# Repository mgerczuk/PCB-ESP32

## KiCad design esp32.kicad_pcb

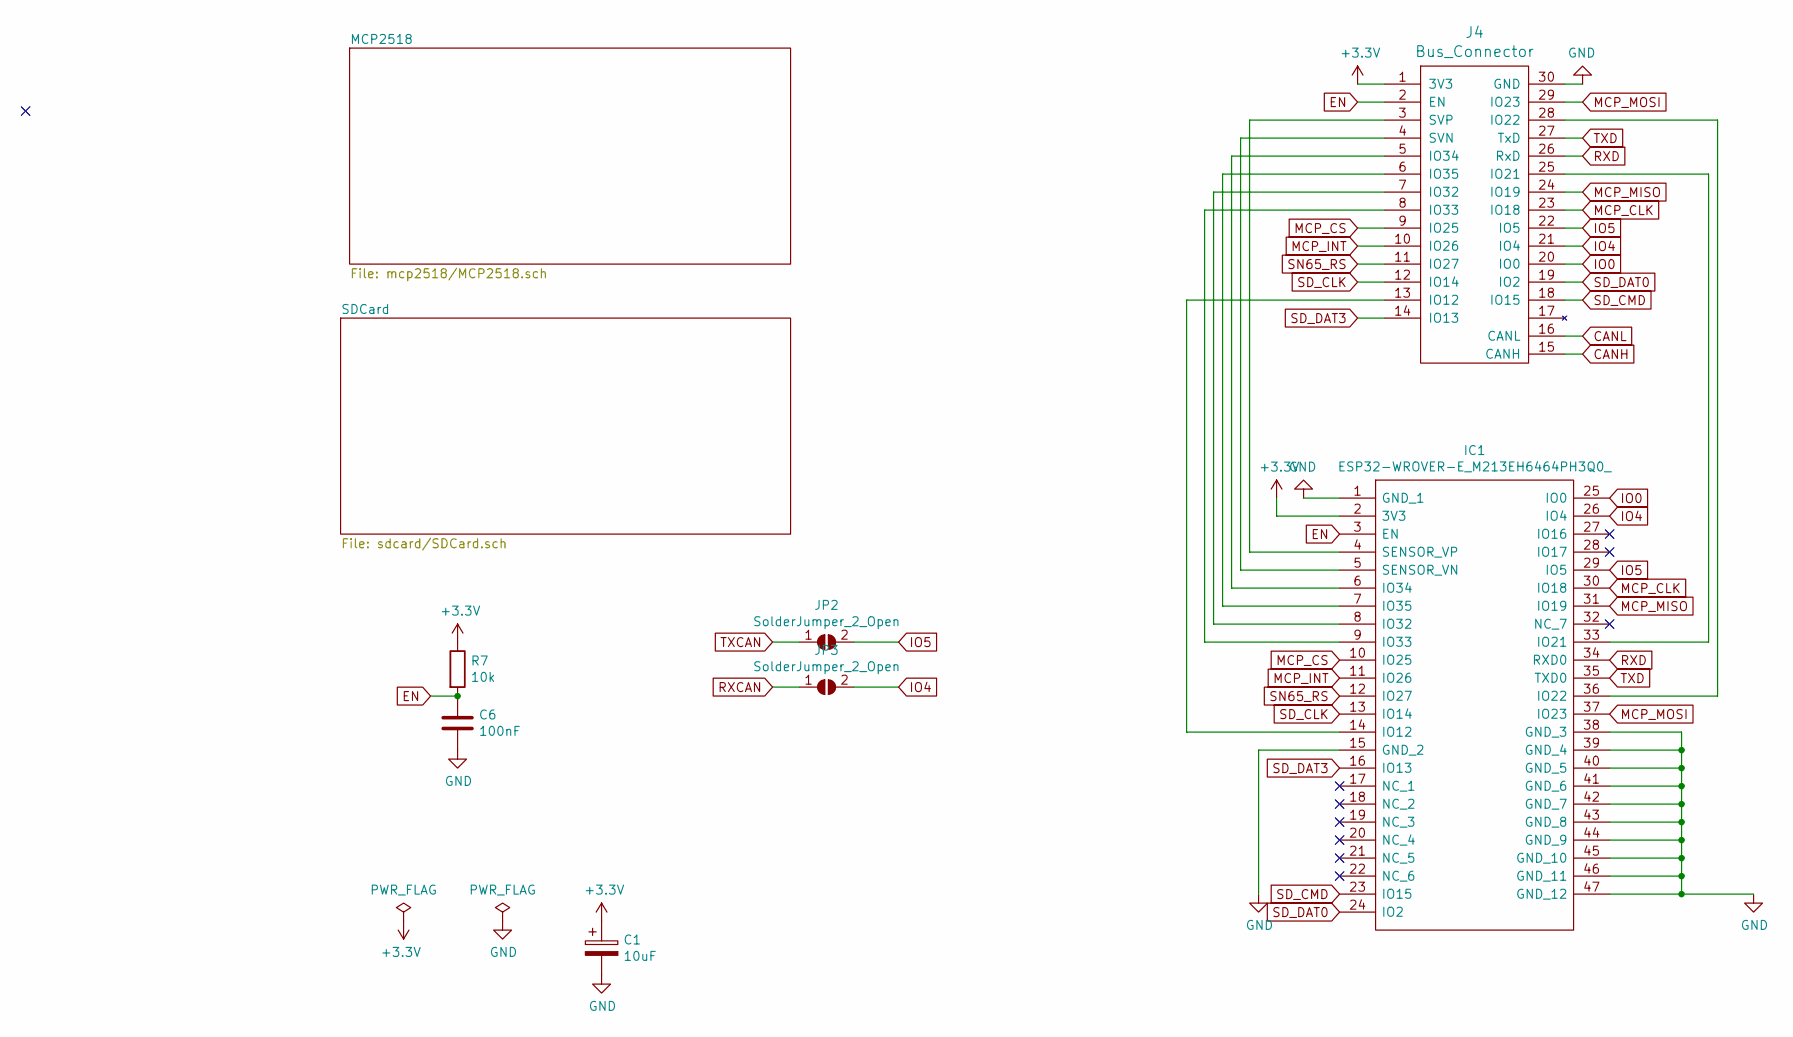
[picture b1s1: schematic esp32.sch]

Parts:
C1: 10uF; CP_EIA-3528-21_Kemet-B_Pad1.50x2.35mm_HandSolder
C6: 100nF; C_0603_1608Metric_Pad1.08x0.95mm_HandSolder
IC1: ESP32-WROVER-E_M213EH6464PH3Q0_; ESP32WROVER; Mouser Part Number 356-ESP32WRVE26464PC
J4: Bus_Connector; PinHeader
JP2, JP3: SolderJumper_2_Open; SolderJumper-2_P1.3mm_Open_RoundedPad1.0x1.5mm
R7: 10k; R_0603_1608Metric_Pad0.98x0.95mm_HandSolder

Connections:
+3V3: C1.1, IC1.2 (3V3), J4.1 (3V3), R7.1; also elsewhere on the board
CANH: J4.15 (CANH); also elsewhere on the board
CANL: J4.16 (CANL); also elsewhere on the board
EN: C6.1, IC1.3 (EN), J4.2 (EN), R7.2
GND: C1.2, C6.2, IC1.1 (GND_1), IC1.15 (GND_2), IC1.38 (GND_3), IC1.39 (GND_4), IC1.40 (GND_5), IC1.41 (GND_6), IC1.42 (GND_7), IC1.43 (GND_8), IC1.44 (GND_9), IC1.45 (GND_10), IC1.46 (GND_11), IC1.47 (GND_12), J4.30 (GND); also elsewhere on the board
IO0: IC1.25 (IO0), J4.20 (IO0)
IO4: IC1.26 (IO4), J4.21 (IO4), JP3.2 (B)
IO5: IC1.29 (IO5), J4.22 (IO5), JP2.2 (B)
MCP_CLK: IC1.30 (IO18), J4.23 (IO18); also elsewhere on the board
MCP_CS: IC1.10 (IO25), J4.9 (IO25); also elsewhere on the board
MCP_INT: IC1.11 (IO26), J4.10 (IO26); also elsewhere on the board
MCP_MISO: IC1.31 (IO19), J4.24 (IO19); also elsewhere on the board
MCP_MOSI: IC1.37 (IO23), J4.29 (IO23); also elsewhere on the board
unnamed: IC1.4 (SENSOR_VP), J4.3 (SVP)
unnamed: IC1.5 (SENSOR_VN), J4.4 (SVN)
unnamed: IC1.6 (IO34), J4.5 (IO34)
unnamed: IC1.7 (IO35), J4.6 (IO35)
unnamed: IC1.8 (IO32), J4.7 (IO32)
unnamed: IC1.9 (IO33), J4.8 (IO33)
unnamed: IC1.14 (IO12), J4.13 (IO12)
unnamed: IC1.33 (IO21), J4.25 (IO21)
unnamed: IC1.36 (IO22), J4.28 (IO22)
RXCAN: JP3.1 (A); also elsewhere on the board
RXD: IC1.34 (RXD0), J4.26 (RxD)
SD_CLK: IC1.13 (IO14), J4.12 (IO14); also elsewhere on the board
SD_CMD: IC1.23 (IO15), J4.18 (IO15); also elsewhere on the board
SD_DAT0: IC1.24 (IO2), J4.19 (IO2); also elsewhere on the board
SD_DAT3: IC1.16 (IO13), J4.14 (IO13); also elsewhere on the board
SN65_RS: IC1.12 (IO27), J4.11 (IO27); also elsewhere on the board
TXCAN: JP2.1 (A); also elsewhere on the board
TXD: IC1.35 (TXD0), J4.27 (TxD)

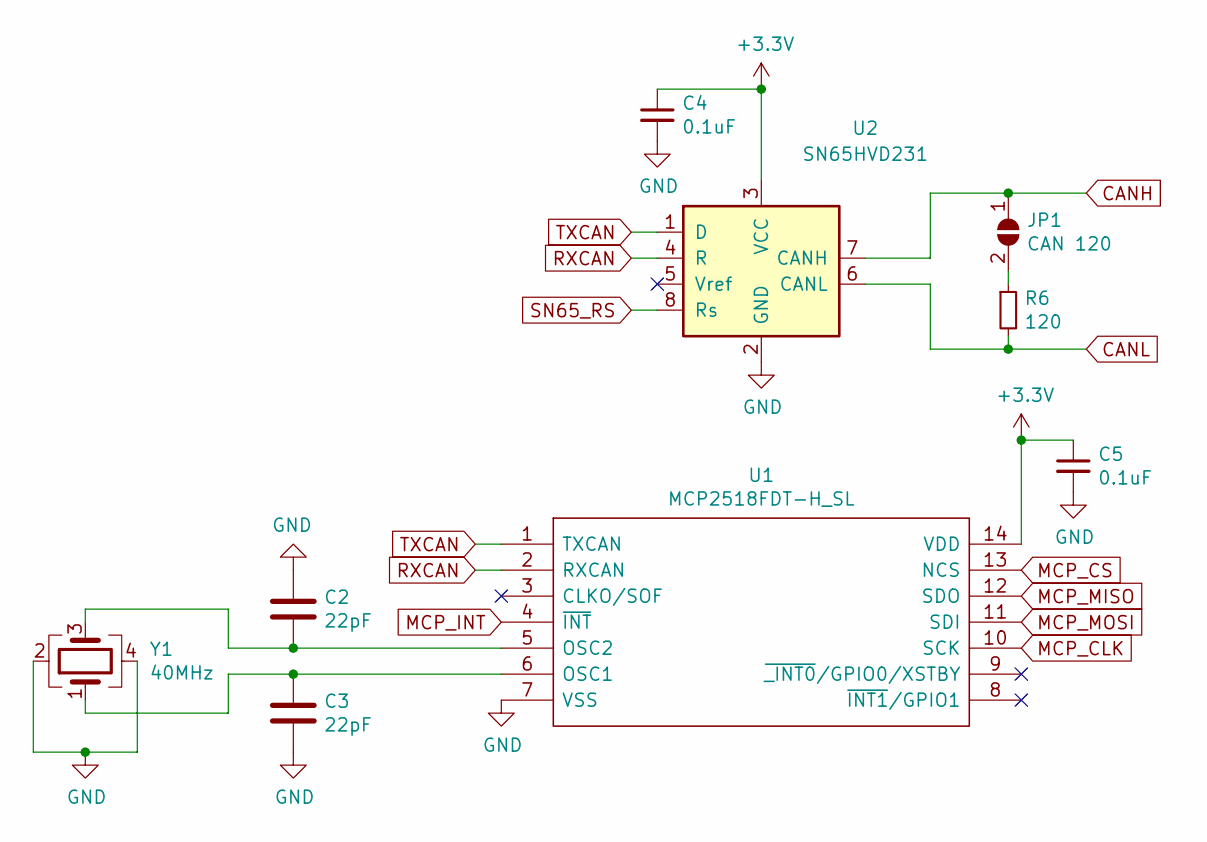
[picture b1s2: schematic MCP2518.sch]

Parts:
C2, C3: 22pF; C_0603_1608Metric_Pad1.08x0.95mm_HandSolder
C4, C5: 0.1uF; C_0603_1608Metric_Pad1.08x0.95mm_HandSolder
JP1: CAN 120; SolderJumper-2_P1.3mm_Open_RoundedPad1.0x1.5mm
R6: 120; R_0603_1608Metric_Pad0.98x0.95mm_HandSolder
U1: MCP2518FDT-H_SL; SOIC127P600X175-14N; Mouser Part Number 579-MCP2518FDT-H/SL
U2: SN65HVD231; SOIC-8_3.9x4.9mm_P1.27mm
Y1: 40MHz; Crystal_SMD_3225-4Pin_3.2x2.5mm

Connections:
+3V3: C4.1, C5.1, U1.14 (VDD), U2.3 (VCC); also elsewhere on the board
CANH: JP1.1 (A), U2.7 (CANH); also elsewhere on the board
CANL: R6.2, U2.6 (CANL); also elsewhere on the board
GND: C2.1, C3.2, C4.2, C5.2, U1.7 (VSS), U2.2 (GND), Y1.2, Y1.4; also elsewhere on the board
MCP_CLK: U1.10 (SCK); also elsewhere on the board
MCP_CS: U1.13 (NCS); also elsewhere on the board
MCP_INT: U1.4 (~INT); also elsewhere on the board
MCP_MISO: U1.12 (SDO); also elsewhere on the board
MCP_MOSI: U1.11 (SDI); also elsewhere on the board
unnamed: C2.2, U1.5 (OSC2), Y1.3
unnamed: C3.1, U1.6 (OSC1), Y1.1
unnamed: JP1.2 (B), R6.1
RXCAN: U1.2 (RXCAN), U2.4 (R); also elsewhere on the board
SN65_RS: U2.8 (Rs); also elsewhere on the board
TXCAN: U1.1 (TXCAN), U2.1 (D); also elsewhere on the board

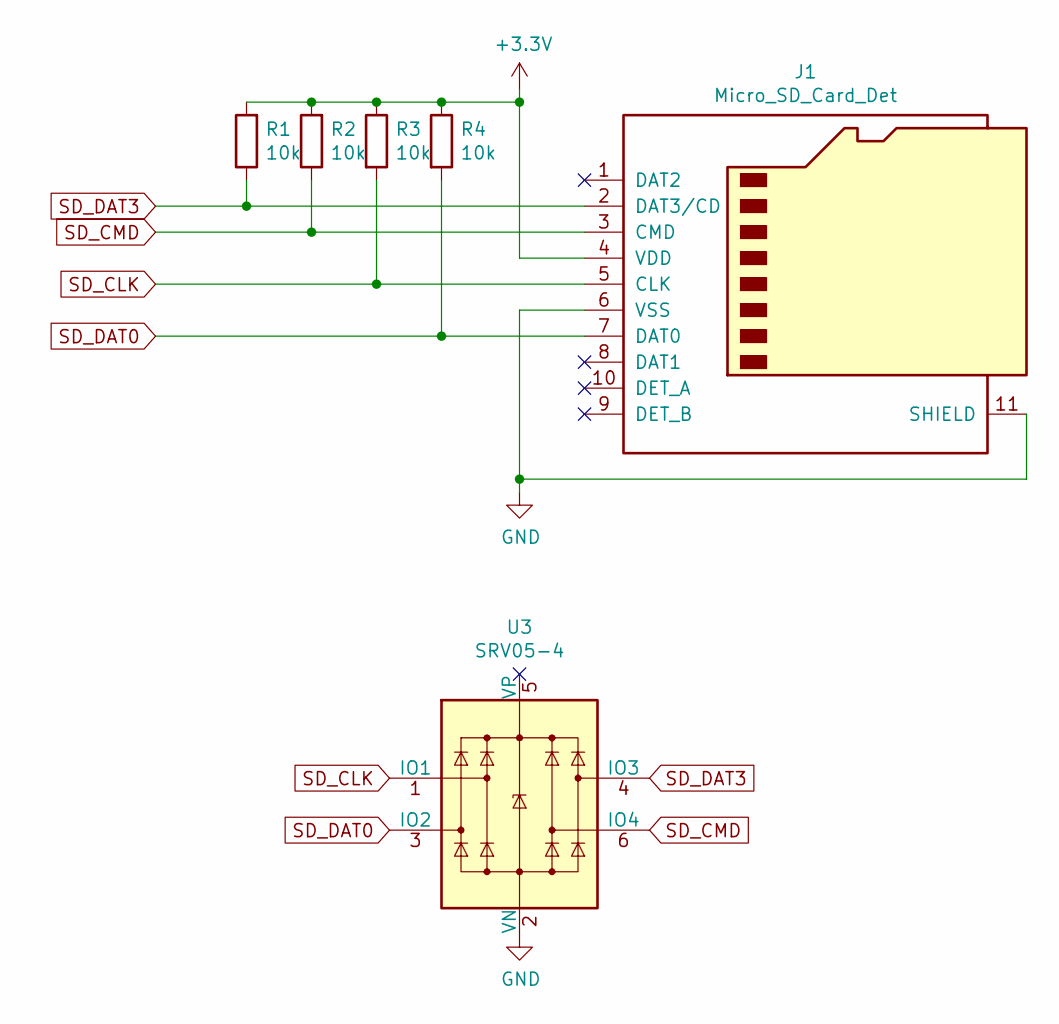
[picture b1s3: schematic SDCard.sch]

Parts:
J1: Micro_SD_Card_Det; SD_CTF-11081-P
R1, R2, R3, R4: 10k; R_0603_1608Metric_Pad0.98x0.95mm_HandSolder
U3: SRV05-4; SOT-23-6

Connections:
+3V3: J1.4 (VDD), R1.2, R2.2, R3.1, R4.1; also elsewhere on the board
GND: J1.6 (VSS), J1.11 (SHIELD), U3.2 (VN); also elsewhere on the board
SD_CLK: J1.5 (CLK), R3.2, U3.1 (IO1); also elsewhere on the board
SD_CMD: J1.3 (CMD), R2.1, U3.6 (IO4); also elsewhere on the board
SD_DAT0: J1.7 (DAT0), R4.2, U3.3 (IO2); also elsewhere on the board
SD_DAT3: J1.2 (DAT3/CD), R1.1, U3.4 (IO3); also elsewhere on the board

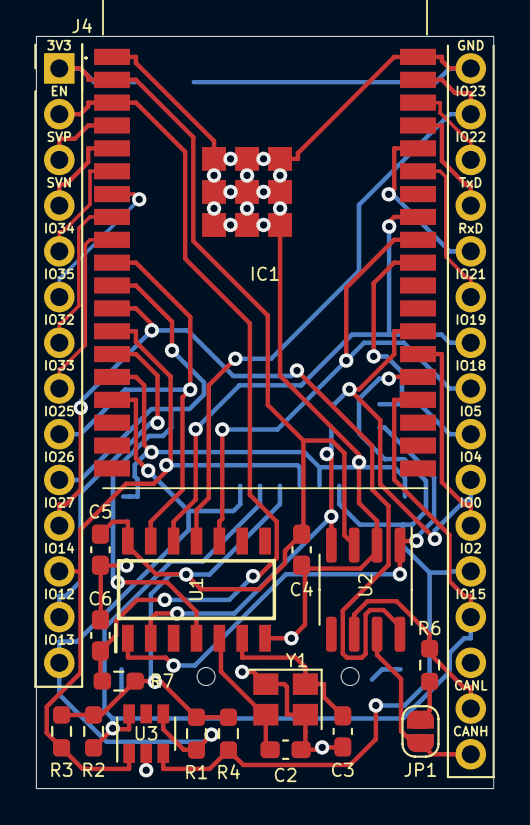
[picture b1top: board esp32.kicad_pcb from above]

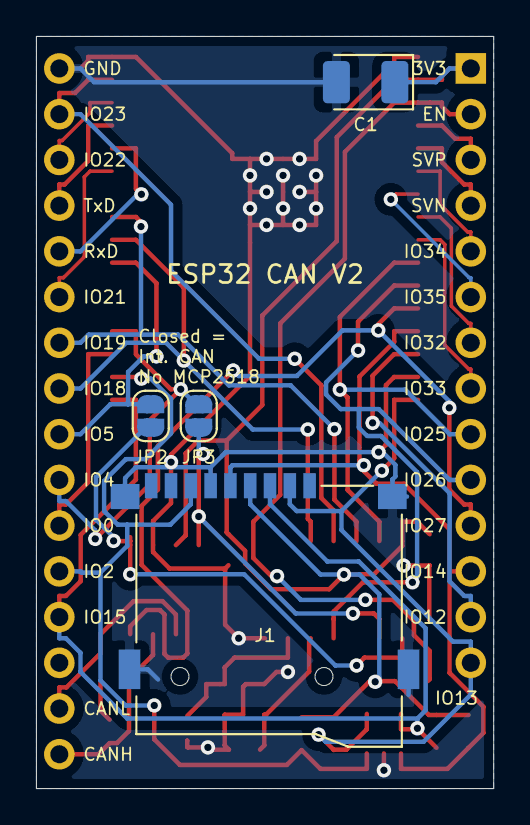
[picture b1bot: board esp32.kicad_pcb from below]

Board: 2 copper layers, 25.4 x 41.8 mm, 22 parts (4 on the bottom side), 34 nets.

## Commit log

2021-07-09 Erster Commit
2021-07-11 EN Pullup, DTR + RTS
2021-07-16 Alle ESP Pins
2021-07-20 ESP32 Bus extrahiert
2021-07-23 SD Card und MCP extrahiert
2021-07-24 Aktualisiert mit master
2021-07-24 Gerber erzeugt
2021-07-26 Gerber mit korrekter Erweiterung
2021-08-06 Footprints für "Hand solder" Wahlweise MCP2518 oder interner CAN
2021-09-10 Ausdruck Bestückung verbessert
2021-10-15 - SN65 RS an GPIO 27 - Quarz Footprint 3225
2021-11-05 Gerbers erstellt
2021-11-12 Beschriftung zugefügt
2021-11-12 Gerber erstellt
